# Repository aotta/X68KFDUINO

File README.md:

# X68KFDUINO
External floppy disk adapter for Sharp X68000, based on Arduino Nano

Use 2 buttons to give X68k the insert/eject signals: you have to eject the virtual floppy (turn off green led) when led flashes, select the image on HxC/Gotek, then re-insert the virtual floppy (Green led re-turned on).
This for disk 1 or 2, as needed.

More info on nfg.forums : https://nfggames.com/forum2/index.php?topic=7225.0

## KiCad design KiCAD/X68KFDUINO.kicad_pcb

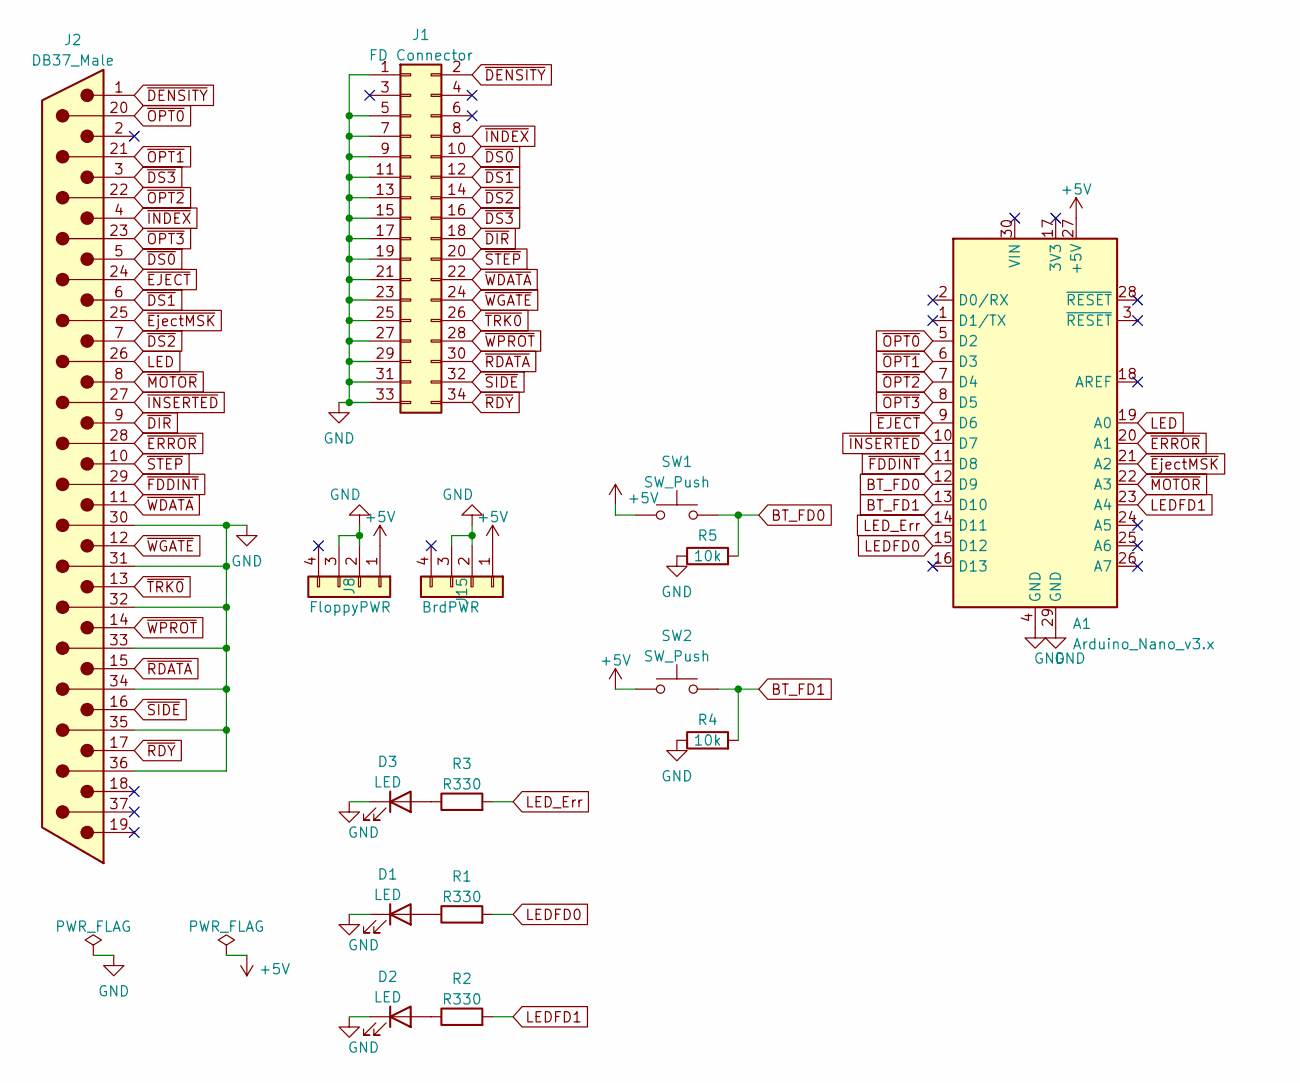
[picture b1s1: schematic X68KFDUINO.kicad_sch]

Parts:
A1: Arduino_Nano_v3.x; Arduino_Nano
D1, D2, D3: LED; LED_D3.0mm
J1: FD Connector; IDC-Header_2x17_P2.54mm_Horizontal
J2: DB37_Male; DSUB-37_Male_Horizontal_P2.77x2.84mm_EdgePinOffset4.94mm_Ho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
J8: FloppyPWR; PinHeader_1x04_P2.54mm_Horizontal
J15: BrdPWR; PinHeader_1x04_P2.54mm_Horizontal
R1, R2, R3: R330; R_Axial_DIN0207_L6.3mm_D2.5mm_P7.62mm_Horizontal
R4, R5: 10k; R_Axial_DIN0207_L6.3mm_D2.5mm_P7.62mm_Horizontal
SW1, SW2: SW_Push; SW_Tactile_SPST_Angled_PTS645Vx83-2LFS

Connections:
+5V: A1.27 (+5V), J8.1, J15.1, SW1.1, SW2.1
BT_FD0: A1.12 (D9), R5.2, SW1.2
BT_FD1: A1.13 (D10), R4.2, SW2.2
GND: A1.4 (GND), A1.29 (GND), D1.1 (K), D2.1 (K), D3.1 (K), J1.1, J1.5, J1.7, J1.9, J1.11, J1.13, J1.15, J1.17, J1.19, J1.21, J1.23, J1.25, J1.27, J1.29, J1.31, J1.33, J2.30, J2.31, J2.32, J2.33, J2.34, J2.35, J2.36, J8.2, J8.3, J15.2, J15.3, R4.1, R5.1
LED: A1.19 (A0), J2.26
LEDFD0: A1.15 (D12), R1.2
LEDFD1: A1.23 (A4), R2.2
LED_Err: A1.14 (D11), R3.2
unnamed: D1.2 (A), R1.1
unnamed: D2.2 (A), R2.1
unnamed: D3.2 (A), R3.1
~DENSITY: J1.2, J2.1
~DIR: J1.18, J2.9
~DS0: J1.10, J2.5
~DS1: J1.12, J2.6
~DS2: J1.14, J2.7
~DS3: J1.16, J2.3
~EJECT: A1.9 (D6), J2.24
~ERROR: A1.20 (A1), J2.28
~EjectMSK: A1.21 (A2), J2.25
~FDDINT: A1.11 (D8), J2.29
~INDEX: J1.8, J2.4
~INSERTED: A1.10 (D7), J2.27
~MOTOR: A1.22 (A3), J2.8
~OPT0: A1.5 (D2), J2.20
~OPT1: A1.6 (D3), J2.21
~OPT2: A1.7 (D4), J2.22
~OPT3: A1.8 (D5), J2.23
~RDATA: J1.30, J2.15
~RDY: J1.34, J2.17
~SIDE: J1.32, J2.16
~STEP: J1.20, J2.10
~TRK0: J1.26, J2.13
~WDATA: J1.22, J2.11
~WGATE: J1.24, J2.12
~WPROT: J1.28, J2.14

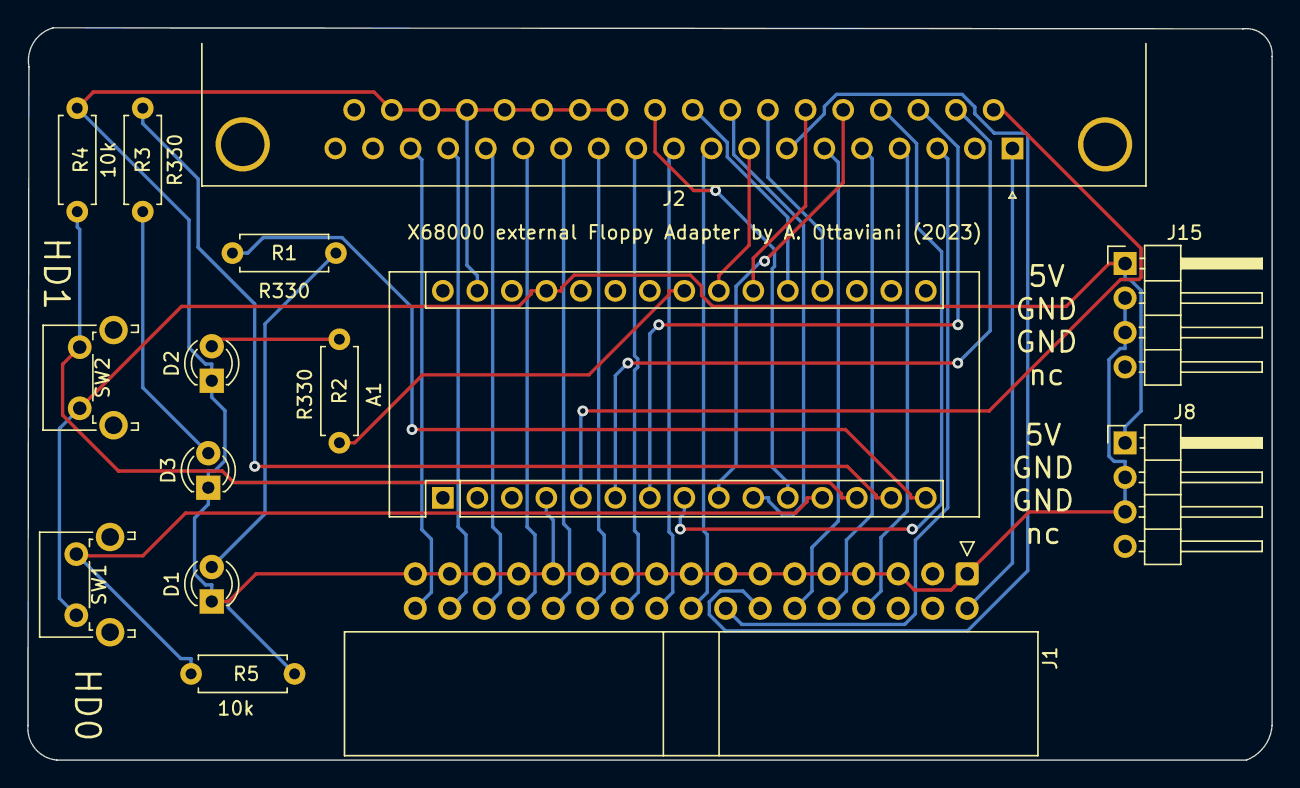
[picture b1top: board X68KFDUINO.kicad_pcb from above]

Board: 2 copper layers, 91.6 x 53.9 mm, 15 parts (0 on the bottom side), 36 nets.

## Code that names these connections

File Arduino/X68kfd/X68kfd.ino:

/*
 * X68KFDINO - External FD adapter for Sharp X68000
 * by Andrea Ottaviani june 2023
 * 
 * 
Access/Write strobe :

/OPTION_SEL_X : "Chip select" for the extra functions of drive DSX (X: 0-3)

Input / functions signals :

/EJECT_FUNC : If this signal is low when OPTION_SEL_X is asserted, the disk will be ejected.
/LOCK_FUNC (Eject MSK?): If this signal is low when OPTION_SEL_X is asserted, the disk will be locked (eject button off). If this signal is high when OPTION_SEL_X is asserted the disk will be unlocked (eject button on).
/BLINK_FUNC : If this signal is low when OPTION_SEL_X is asserted, the LED blink. If this signal is high when OPTION_SEL_X is asserted, the LED stop blinking.

Output signals (drive status):

/DISK_IN_DRIVE : when OPTION_SEL_X is asserted : Low = a disk in the drive. High = No disk.
/INSERT_FAULT : when OPTION_SEL_X is asserted : Low = a disk insert failure occured . High = No problem. This status is cleared at the rising edge of OPTION_SEL_X.

Output signal (Interrupt line):

/INT : Interrupt line : This signal is activated at each disk status change (inserted/ejected). The interrupt is cleared at the rising edge of /OPTION_SEL_X. (Note : more than one drive can activate this line in the same time -> Softwares scan all disk drive at each /INT assertion).

Note 1: For proper operation all output should be able to drive 5/150=33mA since 150 ohms pull-up are used.
Note 2: The X68000 /OPTION_SEL_X assertion duration is ~2.5us per access. This can depend of the software, the CPU speed.
 */


//Cablage
#define OPT0                2  // Set D2 as OPT0 Read strobe
#define OPT1                3  // Set D3 as OPT1 Read strobe
#define OPT2                4  // Set D4 as OPT2 Read strobe
#define OPT3                5  // Set D5 as OPT3 Read strobe
#define Eject               6  // Set D6 as Eject Read strobe
#define Inserted            7 // Set D7 as Inserted Read strobe
#define FDDINT              8   // Set D8 as FD Interrupt Read strobe
#define BT_FD0              9  // Set D9 as Button FD0 Read strobe
#define BT_FD1             10  // Set D10 as Button FD1 Read strobe
#define LED_RED            11  // Set D11 as LED_RED output (RED LED)
#define LEDFD0            12  // Set D12 as LED FD0 output (Green LED)
#define LED_BLINK          A0  // Set A0 as LED (Blink) output
#define Error              A1  // Set A1 as Error Read strobe
#define EjectMSK           A2  // Set A2 as EjectMSK Read strobe
#define Motor              A3  // Set A3 as Motor Read strobe
#define LEDFD1             A4  // Set A4 as LED FD1 output (Green LED)


void setup() {
  // put your setup code here, to run once:
  // initialize digital pin 13 as an output.
  pinMode(OPT0, INPUT);
  pinMode(OPT1, INPUT);
  pinMode(OPT2, INPUT);
  pinMode(OPT3, INPUT);
  pinMode(Eject, INPUT);
  pinMode(BT_FD0, INPUT);
  pinMode(BT_FD1, INPUT);
  pinMode(LED_BLINK, INPUT); // Blink
  pinMode(EjectMSK, INPUT); // LOCK (Red led)
  pinMode(Motor, INPUT); // 
  pinMode(Inserted, OUTPUT);
  pinMode(FDDINT, OUTPUT);
  pinMode(LED_RED, OUTPUT); // used for LED LOCK, Red light
  pinMode(LEDFD0, OUTPUT);
  pinMode(Error, OUTPUT);
  pinMode(LEDFD1, OUTPUT);

  Serial.begin(115200);

}

void loop() {
  unsigned int LDF0=0; // 0=unlocked, 1=locked
  unsigned int LDF1=0; // 0=unlocked, 1=locked
  unsigned int DF0=1; // 0=eject, 1=insert, 2=lock, 3=blink
  unsigned int DF1=1; // 0=eject, 1=insert, 2=lock, 3=blink
  unsigned int bit0Eject=0;
  unsigned int bit0Msk=0;
  unsigned int bit0Blink=0;
  unsigned int bit1Eject=0;
  unsigned int bit1Msk=0;
  unsigned int bit1Blink=0;
  unsigned int dint=30; //30 ok x drakula e ajax
  unsigned int dblink=50;  //50 ok x drakula e ajax
  
  // put your main code here, to run repeatedly:

 while(1) {

   digitalWrite(Inserted,HIGH);
  // digitalWrite(Error,LOW); needed for nemesis 90 kay?
 
   if ((digitalRead(BT_FD0)==HIGH)&&(LDF0==0)) {
     bit0Blink=0;
     if (DF0==1) {
        DF0=0;
      } else {
        DF0=1;
      }
    Serial.print("DF0:");Serial.println(DF0);
    delay(600);
    }

  if ((digitalRead(BT_FD1)==HIGH)&&(LDF1==0)) {
      bit1Blink=0;
      if (DF1==1) {
        DF1=0;
      } else {
        DF1=1;
      }
    Serial.print("DF1:");Serial.println(DF1);
    delay(600);
    }

   if (digitalRead(OPT0)==LOW) {
     if (digitalRead(Eject)==LOW) {
       DF0=0;
       bit0Blink=0;
       Serial.print("Ej 0-");
    }
    
    if (digitalRead(EjectMSK)==LOW) {
      LDF0=1;
    //  Serial.println("MSK0");
      digitalWrite(LED_RED,HIGH);
    } else {
      LDF0=0;
      digitalWrite(LED_RED,LOW);
    }
 
    if (digitalRead(LED_BLINK)==LOW) {
       bit0Blink=1;
       digitalWrite(LEDFD0,LOW); 
        delay(dblink);   // low for A-JAX
       digitalWrite(LEDFD0,HIGH);
     //  Serial.println("Blk 0-"); 
    }

    
    if (DF0==0) {
       digitalWrite(FDDINT,LOW);
       digitalWrite(LEDFD0,LOW);
      } else {
       if (bit0Blink==0) {
         digitalWrite(Inserted,LOW);
       //  Serial.print("df0-IN");
         digitalWrite(Error,HIGH);
         digitalWrite(FDDINT,HIGH);
         digitalWrite(LEDFD0,HIGH);
         delay(dint); // to receipt from X68k?
             } else {
          digitalWrite(FDDINT,LOW);
          digitalWrite(LEDFD0,HIGH); 
         }
      }
  }  // opt 0

 if (digitalRead(OPT1)==LOW) {
  if (digitalRead(Eject)==LOW) {
      DF1=0;
      bit1Blink=0;
      Serial.print("Ej 1-");
    }
    
  if (digitalRead(EjectMSK)==LOW) {
      LDF1=1;
    //  Serial.println("MSK1");
    digitalWrite(LED_RED,HIGH);
  } else {
      LDF1=0;
      digitalWrite(LED_RED,LOW);
    }
    
  if (digitalRead(LED_BLINK)==LOW) {
       bit1Blink=1;
       digitalWrite(LEDFD1,LOW); 
     delay(dblink);
      // digitalWrite(LEDFD1,HIGH); 
      //Serial.print("Blk 1-");
       }
    
       if (DF1==0) {
       digitalWrite(FDDINT,LOW);
       digitalWrite(LEDFD1,LOW);
      } else {
       if (bit1Blink==0) {
         digitalWrite(Inserted,LOW);
        //  Serial.print("df1-IN");
         digitalWrite(Error,HIGH);
         digitalWrite(FDDINT,HIGH);
         digitalWrite(LEDFD1,HIGH);
         delay(dint); // to receipt from X68k?
          } else {
          digitalWrite(LEDFD1,HIGH); 
         }
      }
  
  } //opt1
  
 } //while
 
}

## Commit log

2023-06-02 Add files via upload
    First upload
